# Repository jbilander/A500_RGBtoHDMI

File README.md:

# A500_RGBtoHDMI
My RGBtoHDMI-adapter-board design for A500.

***

<br />

***

<br />

***

<br />

***

### Build

<br />

<br />

<br />

<br />

<br />

<br />

***

Video: <br />

https://drive.google.com/file/d/1ksP-LVyoxUxEtZK_JW-vs8qUCuZv387j/view?usp=sharing

***

### RPi Zero configuration

Follow the instructions here:

https://github.com/hoglet67/RGBtoHDMI/wiki/Quick-Start-Guide#installing-the-software

...and then...

To auto configure for correct profile and operation with single button, copy the files in the appropriate Amiga folder into the root folder, overwriting any existing files.

***

BOM Rev. 1A
---------
Position  | Name/Value   | Package | Notes
-|-|-|-|
U1 | 2x24 Round Female Pin Header Connector | 1x40 2.54mm pitch | Cut down to 2x24 Pin for socketing Denise
U2 | XC9572XL-10VQ64 | VQFP-64 | Xilinx 72-mc CPLD 52 I/O
U3 | LM1117-3.3 or AMS1117-3.3 | SOT-223 | 3.3V 1A Low Drop-Out (LDO) Voltage regulator.
U4 | 2x24 Single Row Male Pin Connector Strip | 1x40 2.54mm pitch | Cut down to 2x24 Pin
J1 | 2X20 Pin Double Row Straight Female Pin Header 2.54mm pitch | 2x20 2.54mm pitch | [2x20 Pin Header](https://www.aliexpress.com/item/32854215610.html)
R1 | 1k | 0805 | Pull-down resistor (SPDATA)
R2 | 4.7k | 0805 | Pull-down resistor (DETECT)
C1 | 10uF | 1206 | 5V Decoupling capacitor
C2 | 10uF | 1206 | 3V3 Decoupling capacitor
C3 | 0.1uF = 100nF | 0805 | 3V3 Decoupling capacitor
C4 | 0.1uF = 100nF | 0805 | 3V3 Decoupling capacitor
C5 | 0.1uF = 100nF | 0805 | 3V3 Decoupling capacitor
C6 | 0.1uF = 100nF | 0805 | 3V3 Decoupling capacitor
JTAG | JTAG Pin Header | 2.54mm pitch | (Optional) Hold JTAG-header against holes while programming is enough.
PWR | VCC/GND-header | 2.00mm pitch | A 2.54mm two-pin header fits surface mounted on pads

Cable:
Ribbon FPV HDMI-Compatible Connector Flexible Flat Cable<br />
https://www.aliexpress.com/item/4000014554460.html<br />
* FFC 10cm (or whatever length you prefer, cable on pic is 10cm)<br />
* Connector-A4<br />
* Connector-C1<br />

***

Happy Hackin'

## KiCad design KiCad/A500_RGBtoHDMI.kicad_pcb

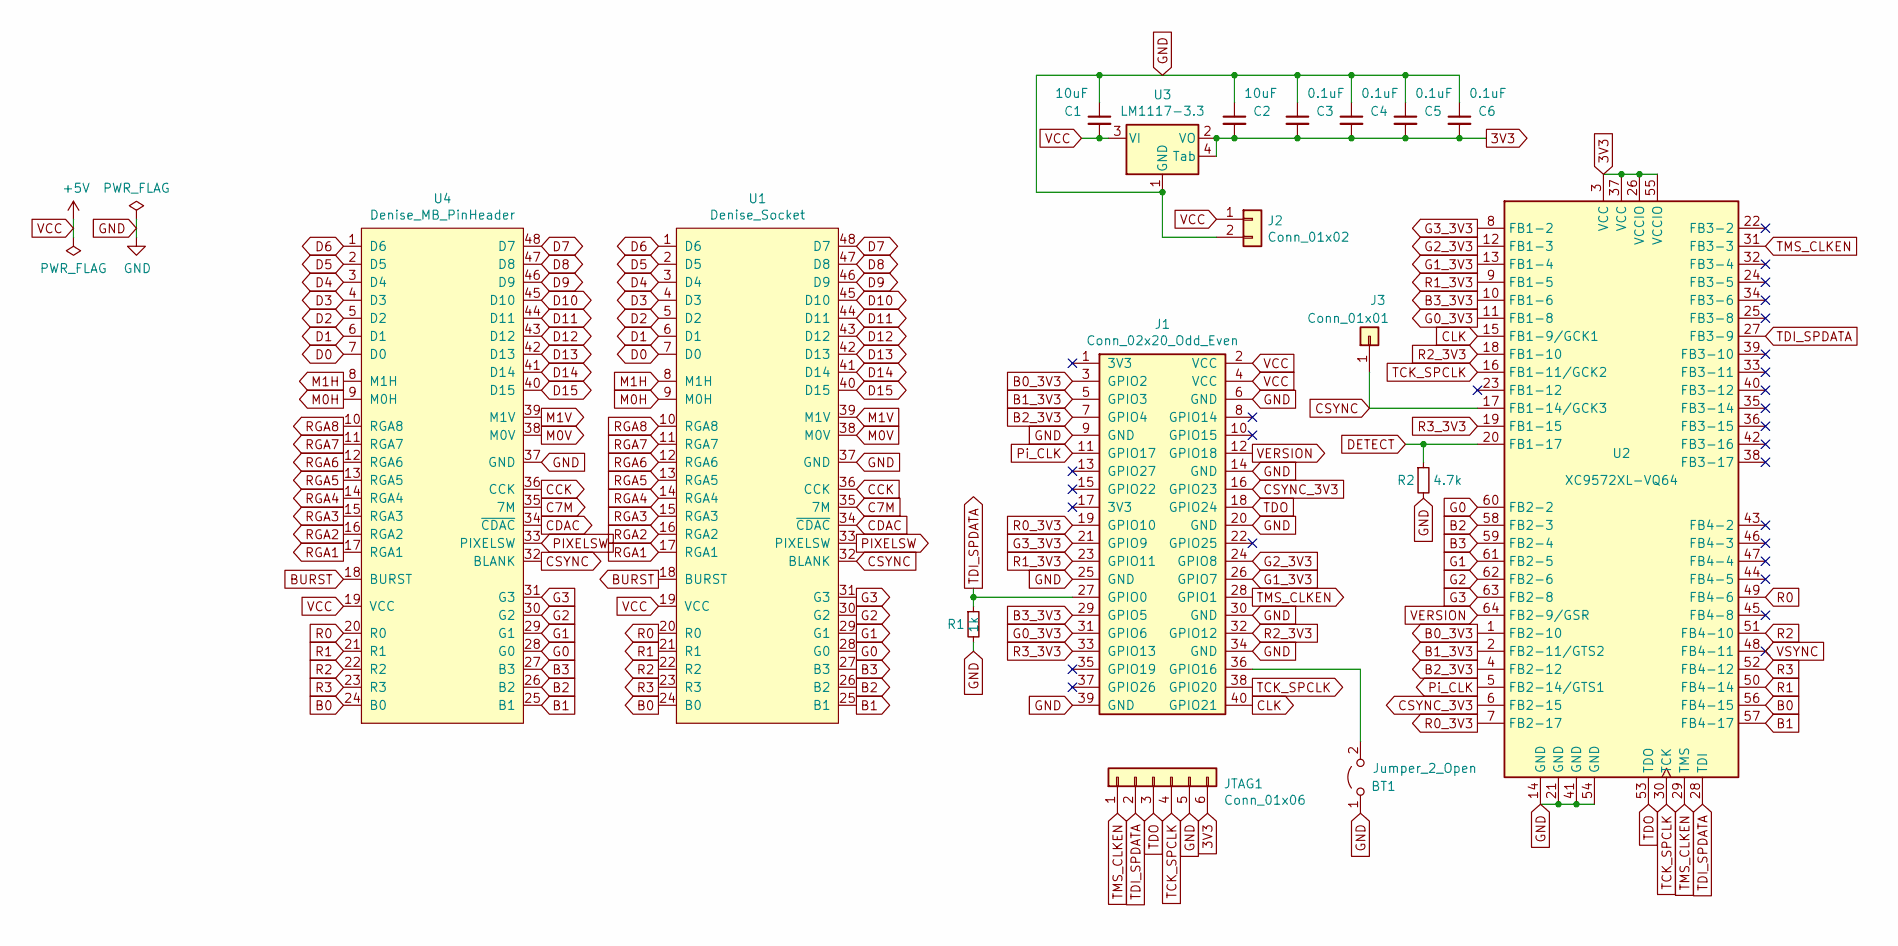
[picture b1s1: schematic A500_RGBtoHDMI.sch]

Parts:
BT1: Jumper_2_Open; PinHeader_1x02_P2.54mm_Horizontal
C1, C2: 10uF; C_1206_3216Metric_Pad1.42x1.75mm_HandSolder
C3, C4, C5, C6: 0.1uF; C_0805_2012Metric_Pad1.15x1.40mm_HandSolder
J1: Conn_02x20_Odd_Even; PinSocket_2x20_P2.54mm_Vertical
J2: Conn_01x02; PinHeader_1x02_P2.00mm_Vertical
J3: Conn_01x01; PinHeader_1x01_P2.54mm_Horizontal
JTAG1: Conn_01x06; PinHeader_1x06_P2.54mm_Vertical
R1: 1k; R_0805_2012Metric_Pad1.15x1.40mm_HandSolder
R2: 4.7k; R_0805_2012Metric_Pad1.15x1.40mm_HandSolder
U1: Denise_Socket; DIP-48_W15.24mm_Socket_LongPads
U2: XC9572XL-VQ64; TQFP-64_10x10mm_P0.5mm
U3: LM1117-3.3; SOT-223
U4: Denise_MB_PinHeader; DIP-48_W15.24mm_LongPads

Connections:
3V3: C2.2, C3.2, C4.2, C5.2, C6.2, JTAG1.6, U2.3 (VCC), U2.26 (VCCIO), U2.37 (VCC), U2.55 (VCCIO), U3.2 (VO), U3.4 (Tab)
B0: U1.24 (B0), U2.56 (FB4-15), U4.24 (B0)
B0_3V3: J1.3 (GPIO2), U2.1 (FB2-10)
B1: U1.25 (B1), U2.57 (FB4-17), U4.25 (B1)
B1_3V3: J1.5 (GPIO3), U2.2 (FB2-11/GTS2)
B2: U1.26 (B2), U2.58 (FB2-3), U4.26 (B2)
B2_3V3: J1.7 (GPIO4), U2.4 (FB2-12)
B3: U1.27 (B3), U2.59 (FB2-4), U4.27 (B3)
B3_3V3: J1.29 (GPIO5), U2.10 (FB1-6)
BURST: U1.18 (BURST), U4.18 (BURST)
C7M: U1.35 (7M), U4.35 (7M)
CCK: U1.36 (CCK), U4.36 (CCK)
CDAC: U1.34 (~CDAC), U4.34 (~CDAC)
CLK: J1.40 (GPIO21), U2.15 (FB1-9/GCK1)
CSYNC: J3.1, U1.32 (BLANK), U2.17 (FB1-14/GCK3), U4.32 (BLANK)
CSYNC_3V3: J1.16 (GPIO23), U2.6 (FB2-15)
D0: U1.7 (D0), U4.7 (D0)
D1: U1.6 (D1), U4.6 (D1)
D2: U1.5 (D2), U4.5 (D2)
D3: U1.4 (D3), U4.4 (D3)
D4: U1.3 (D4), U4.3 (D4)
D5: U1.2 (D5), U4.2 (D5)
D6: U1.1 (D6), U4.1 (D6)
D7: U1.48 (D7), U4.48 (D7)
D8: U1.47 (D8), U4.47 (D8)
D9: U1.46 (D9), U4.46 (D9)
D10: U1.45 (D10), U4.45 (D10)
D11: U1.44 (D11), U4.44 (D11)
D12: U1.43 (D12), U4.43 (D12)
D13: U1.42 (D13), U4.42 (D13)
D14: U1.41 (D14), U4.41 (D14)
D15: U1.40 (D15), U4.40 (D15)
DETECT: R2.1, U2.20 (FB1-17)
G0: U1.28 (G0), U2.60 (FB2-2), U4.28 (G0)
G0_3V3: J1.31 (GPIO6), U2.11 (FB1-8)
G1: U1.29 (G1), U2.61 (FB2-5), U4.29 (G1)
G1_3V3: J1.26 (GPIO7), U2.13 (FB1-4)
G2: U1.30 (G2), U2.62 (FB2-6), U4.30 (G2)
G2_3V3: J1.24 (GPIO8), U2.12 (FB1-3)
G3: U1.31 (G3), U2.63 (FB2-8), U4.31 (G3)
G3_3V3: J1.21 (GPIO9), U2.8 (FB1-2)
GND: BT1.1 (A), C1.1, C2.1, C3.1, C4.1, C5.1, C6.1, J1.6 (GND), J1.9 (GND), J1.14 (GND), J1.20 (GND), J1.25 (GND), J1.30 (GND), J1.34 (GND), J1.39 (GND), J2.2, JTAG1.5, R1.2, R2.2, U1.37 (GND), U2.14 (GND), U2.21 (GND), U2.41 (GND), U2.54 (GND), U3.1 (GND), U4.37 (GND)
M0H: U1.9 (M0H), U4.9 (M0H)
M0V: U1.38 (M0V), U4.38 (M0V)
M1H: U1.8 (M1H), U4.8 (M1H)
M1V: U1.39 (M1V), U4.39 (M1V)
unnamed: BT1.2 (B), J1.36 (GPIO16)
PIXELSW: U1.33 (PIXELSW), U4.33 (PIXELSW)
Pi_CLK: J1.11 (GPIO17), U2.5 (FB2-14/GTS1)
R0: U1.20 (R0), U2.49 (FB4-6), U4.20 (R0)
R0_3V3: J1.19 (GPIO10), U2.7 (FB2-17)
R1: U1.21 (R1), U2.50 (FB4-14), U4.21 (R1)
R1_3V3: J1.23 (GPIO11), U2.9 (FB1-5)
R2: U1.22 (R2), U2.51 (FB4-10), U4.22 (R2)
R2_3V3: J1.32 (GPIO12), U2.18 (FB1-10)
R3: U1.23 (R3), U2.52 (FB4-12), U4.23 (R3)
R3_3V3: J1.33 (GPIO13), U2.19 (FB1-15)
RGA1: U1.17 (RGA1), U4.17 (RGA1)
RGA2: U1.16 (RGA2), U4.16 (RGA2)
RGA3: U1.15 (RGA3), U4.15 (RGA3)
RGA4: U1.14 (RGA4), U4.14 (RGA4)
RGA5: U1.13 (RGA5), U4.13 (RGA5)
RGA6: U1.12 (RGA6), U4.12 (RGA6)
RGA7: U1.11 (RGA7), U4.11 (RGA7)
RGA8: U1.10 (RGA8), U4.10 (RGA8)
TCK_SPCLK: J1.38 (GPIO20), JTAG1.4, U2.16 (FB1-11/GCK2), U2.30 (TCK)
TDI_SPDATA: J1.27 (GPIO0), JTAG1.2, R1.1, U2.27 (FB3-9), U2.28 (TDI)
TDO: J1.18 (GPIO24), JTAG1.3, U2.53 (TDO)
TMS_CLKEN: J1.28 (GPIO1), JTAG1.1, U2.29 (TMS), U2.31 (FB3-3)
VCC: C1.2, J1.2 (VCC), J1.4 (VCC), J2.1, U1.19 (VCC), U3.3 (VI), U4.19 (VCC)
VERSION: J1.12 (GPIO18), U2.64 (FB2-9/GSR)
VSYNC: U2.48 (FB4-11)

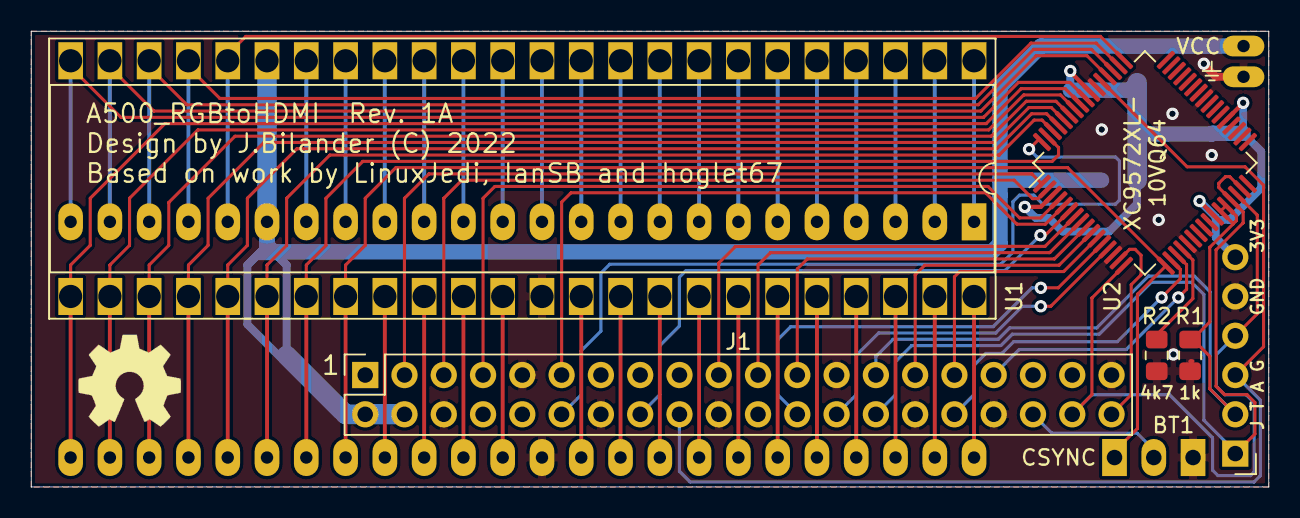
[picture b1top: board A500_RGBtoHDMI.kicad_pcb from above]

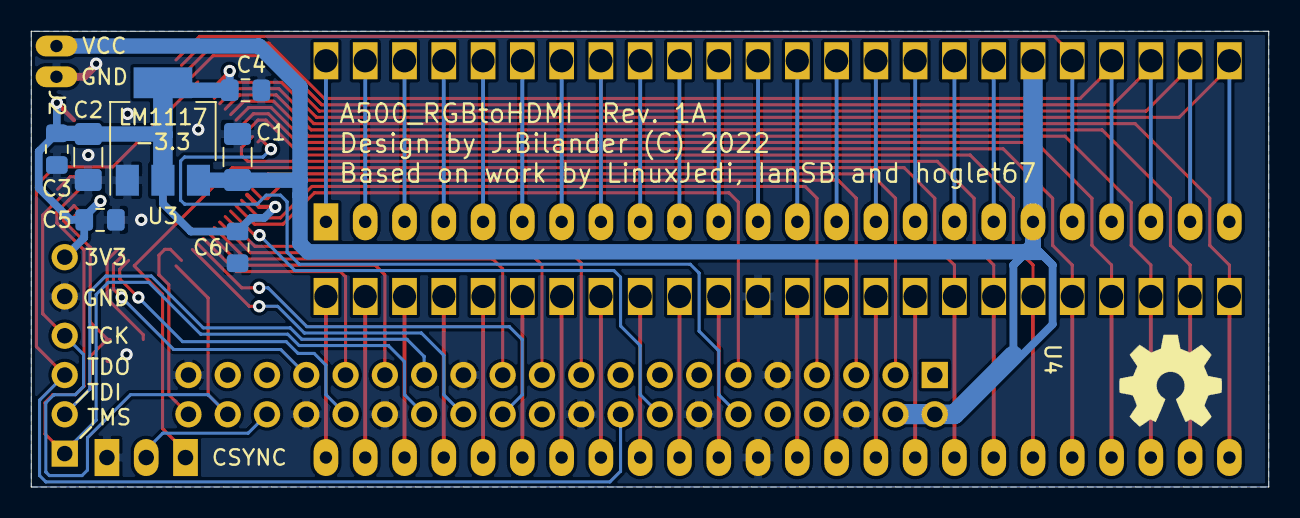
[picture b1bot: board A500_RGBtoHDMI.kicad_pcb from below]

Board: 2 copper layers, 80.0 x 29.5 mm, 17 parts (7 on the bottom side), 71 nets.

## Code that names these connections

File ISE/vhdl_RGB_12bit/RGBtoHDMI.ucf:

# Global Clock Nets
NET "clk" BUFG=CLK;

# Global Clock Nets
NET "sp_clk" BUFG=CLK;

# 96MHz clock domain
NET "clk" TNM_NET = clk_period_grp_1;
TIMESPEC TS_clk_period_1 = PERIOD "clk_period_grp_1" 5.2ns HIGH;

# 10MHz clock domain
#NET "sp_clk" TNM_NET = clk_period_grp_2;
#TIMESPEC TS_clk_period_2 = PERIOD "clk_period_grp_2" 100ns HIGH;

NET "clk"       LOC = "P15";       # input  gpio21 (GCK1)

NET "R3_I"      LOC = "P52";       # input
NET "G3_I"      LOC = "P63";       # input
NET "B3_I"      LOC = "P59";       # input
NET "R2_I"      LOC = "P51";       # input
NET "G2_I"      LOC = "P62";       # input
NET "B2_I"      LOC = "P58";       # input
NET "R1_I"      LOC = "P50";       # input  (was gpio26)
NET "G1_I"      LOC = "P61";       # input  (was gpio19)
NET "B1_I"      LOC = "P57";       # input  (was gpio16)
NET "R0_I"      LOC = "P49";       # input  (was gpio27)
NET "G0_I"      LOC = "P60";       # input  (was gpio25)
NET "B0_I"      LOC = "P56";       # input  (was gpio24)

NET "csync_I"   LOC = "P17";       # input
NET "vsync_I"   LOC = "P48";       # input  (pin assigned but not connected)

NET "analog"    LOC = "P20";       # input  gpio22 (DETECT)

NET "version"   LOC = "P64";       # input  gpio18 (GSR)

NET "sp_clk"    LOC = "P16";       # input  gpio20 (GCK2) (TCK)
NET "sp_data"   LOC = "P27";       # input  gpio0  (input only) (TDI)
NET "sp_clken"  LOC = "P31";       # input  gpio1  (input only) (TMS)

NET "quad(0)"   LOC = "P1";        # output gpio2 (B0_3V3)
NET "quad(1)"   LOC = "P2";        # output gpio3 (B1_3V3)
NET "quad(2)"   LOC = "P4";        # output gpio4 (B2_3V3)
NET "quad(3)"   LOC = "P10";       # output gpio5 (B3_3V3)
NET "quad(4)"   LOC = "P11";       # output gpio6 (G0_3V3)
NET "quad(5)"   LOC = "P13";       # output gpio7 (G1_3V3)
NET "quad(6)"   LOC = "P12";       # output gpio8 (G2_3V3)
NET "quad(7)"   LOC = "P8";        # output gpio9 (G3_3V3)
NET "quad(8)"   LOC = "P7";        # output gpio10 (R0_3V3)
NET "quad(9)"   LOC = "P9";        # output gpio11 (R1_3V3)
NET "quad(10)"  LOC = "P18";       # output gpio12 (R2_3V3)
NET "quad(11)"  LOC = "P19";       # output gpio13 (R3_3V3)

NET "psync"     LOC = "P5";        # output gpio17 (Pi_CLK)
NET "csync"     LOC = "P6";        # output gpio23 (CSYNC_3V3)

NET "quad(0)"   SLOW;
NET "quad(1)"   SLOW;
NET "quad(2)"   SLOW;
NET "quad(3)"   SLOW;
NET "quad(4)"   SLOW;
NET "quad(5)"   SLOW;
NET "quad(6)"   SLOW;
NET "quad(7)"   SLOW;
NET "quad(8)"   SLOW;
NET "quad(9)"   SLOW;
NET "quad(10)"  SLOW;
NET "quad(11)"  SLOW;
NET "psync"     SLOW;
NET "csync"     SLOW;

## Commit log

2022-03-21 added KiCad files
2022-03-21 improved design
2022-03-21 more routing
2022-03-21 added networks to Pi-header
2022-03-21 added CPLD XC9572XL-VQ64 and did more layout and routing
2022-03-22 more routing and fixes
2022-03-23 more routing and small adjustments,fixes and improvements
2022-03-24 added LDO LM1117 3.3V fixed output
2022-03-24 added 100nF decoupling caps to CPLDs 3V3-inputs
2022-03-24 added a two-pin power header VCC/GND
2022-03-25 added Button-jumper (BT1) with 3V3-pull-up resistor
2022-03-25 added DETECT-signal with pull-down resistor
2022-03-26 added 3D-model of RPi Zero
2022-03-26 Updated .gitignore file to ignore output folder named working
2022-03-26 added ISE project src-files from hoglet67 github repo
2022-03-27 add CSYNC-PinHeader for Rev3 A500-mobos
2022-03-27 removed pull-up resistor on BT1 (gpio16), not needed
2022-03-27 some via and silkscreen fixes
2022-03-28 removed hole offset for VCC-header, and some silkscreen fix
2022-03-28 silkscreen fix
2022-04-30 added pics
2022-04-30 added schematic pdf
2022-04-30 Changed package from VQ44 to VQ64
2022-04-30 New pin assignments for VQ64 package
2022-05-01 added pic

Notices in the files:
KiCad/A500_RGBtoHDMI.kicad_pcb:
Design by J.Bilander (C) 2022
